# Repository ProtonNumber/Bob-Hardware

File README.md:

# Bob!

This is the Kicad Repo for Bob, an open-source flight computer and data logger
for model rocketry.

## Specification
- MCU: Raspberry Pi [RP2040](https://datasheets.raspberrypi.com/rp2040/rp2040-datasheet.pdf) Dual Core Cortex M0+.
- Flash: 2 x Wimbond [W25Q128](https://www.winbond.com/resource-files/W25Q128JV%20RevI%2008232021%20Plus.pdf) 16 MiB Flash chips.
- IMU: QST [QMI8658C](https://www.qstcorp.com/upload/pdf/202301/13-52-25%20QMI8658A%20Datasheet%20Rev%20A.pdf) 16 G / 2048 DPS IMU
- Compass: QST [QMC5883L](https://datasheet.lcsc.com/szlcsc/QST-QMC5883L-TR_C192585.pdf)
- Barometer: HopeRF [HP203B](https://hoperf.com/data/upload/portal/20190307/HP203B_DataSheet_EN_V2.0.pdf)
- GPIO: 16 GPIO pins broken out, plus access to internal I2C bus.
- Pyro: 2 x Pyro channels with continuity detection and separate arming switch.

## Pin Assignments
| GPIO Pin | Usage             | Broken Out? | Notes                                             |
|----------|-------------------|-------------|---------------------------------------------------|
| GPIO 00  | -                 | Y           |                                                   |
| GPIO 01  | -                 | Y           |                                                   |
| GPIO 02  | -                 | Y           |                                                   |
| GPIO 03  | -                 | Y           |                                                   |
| GPIO 04  | -                 | Y           |                                                   |
| GPIO 05  | -                 | Y           |                                                   |
| GPIO 06  | -                 | Y           |                                                   |
| GPIO 07  | Fire Main         | N           |                                                   |
| GPIO 08  | Fire Drogue       | N           |                                                   |
| GPIO 09  | Compass Interrupt | N           |                                                   |
| GPIO 10  | IMU Interrupt 1   | N           |                                                   |
| GPIO 11  | IMU Interrupt 2   | N           |                                                   |
| GPIO 12  | I2C SDA           | Y           |                                                   |
| GPIO 13  | I2C SCL           | Y           |                                                   |
| GPIO 14  | Drogue Continuity | N           |                                                   |
| GPIO 15  | Main Continuity   | N           |                                                   |
| GPIO 16  | Flash SPI RX      | N           |                                                   |
| GPIO 17  | Flash SPI CS      | N           |                                                   |
| GPIO 18  | Flash SPI SCLK    | N           |                                                   |
| GPIO 19  | Flash SPI TX      | N           |                                                   |
| GPIO 20  | Buzzer            | N           | Buzzer is only powered when battery is connected. |
| GPIO 21  | Arming Signal     | Y           | Reads status of the ARM switch                    |
| GPIO 22  | -                 | Y           |                                                   |
| GPIO 23  | -                 | Y           |                                                   |
| GPIO 24  | -                 | Y           |                                                   |
| GPIO 25  | Status LED        | N           |                                                   |
| GPIO 26  | -                 | Y           | May be used as analogue input                     |
| GPIO 27  | -                 | Y           | May be used as analogue input                     |
| GPIO 28  | -                 | Y           | May be used as analogue input                     |
| GPIO 29  | -                 | Y           | May be used as analogue input                     |

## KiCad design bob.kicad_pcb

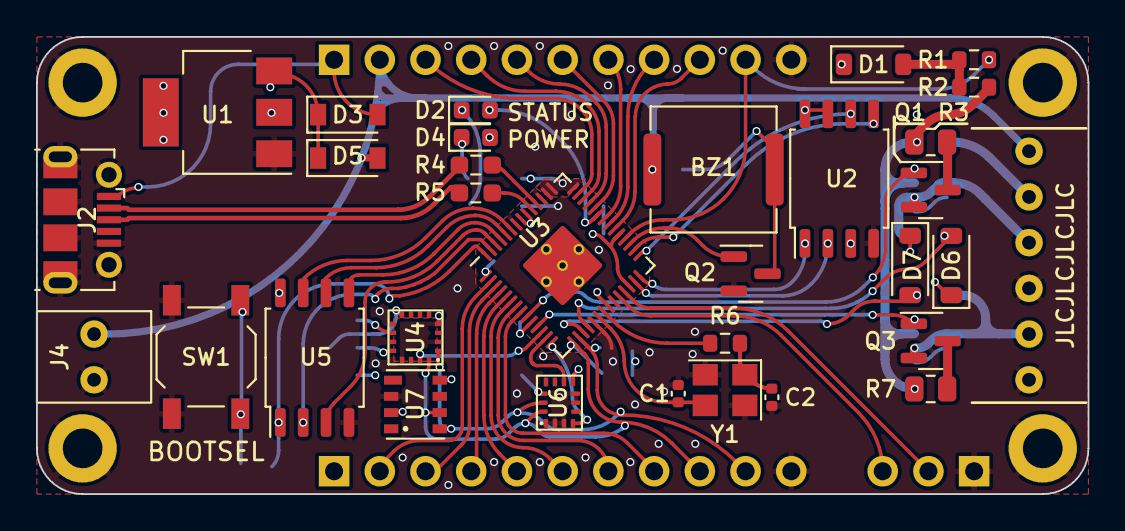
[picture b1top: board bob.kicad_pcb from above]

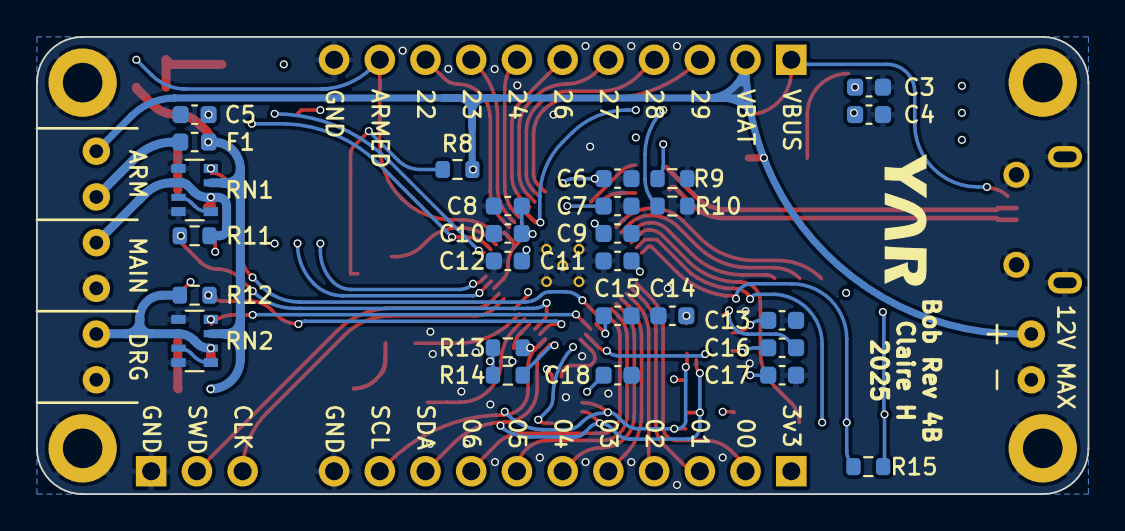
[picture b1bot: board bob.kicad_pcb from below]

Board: 4 copper layers, 58.4 x 25.4 mm, 67 parts (28 on the bottom side), 67 nets.

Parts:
BZ1: Buzzer; CPT-7502-65-SMT-TR
C1, C2: 7p; C_0402_1005Metric
C3, C4: 10u; C_0603_1608Metric
C5, C8, C9, C10, C11, C12, C14, C15, C17, C18: 100n; C_0603_1608Metric
C6, C7: 1u; C_0603_1608Metric
C13: 4.7u; C_0603_1608Metric
C16: 220n; C_0603_1608Metric
D1, D3, D5, D6, D7: B5819W SL; D_SOD-123
D2: GREEN; LED_0603_1608Metric
D4: RED; LED_0603_1608Metric
F1: Polyfuse; Fuse_0603_1608Metric
H1, H2, H3, H4: MountingHole_Pad; MountingHole_2.2mm_M2_DIN965_Pad
J1, J6: GPIO (Optional); PinHeader_1x11_P2.54mm_Vertical
J2: Micro USB Female; USB_Micro-B_Molex-105017-0001
J3: Conn_01x06_Pin; ScrewTerm_2.54x06
J4: Screw Terminal, 2.54mm; ScrewTerm_2.54x02
J5: Conn_01x03_Male; PinHeader_1x03_P2.54mm_Vertical
Q1, Q2, Q3: AO3400A; SOT-23
R1, R2, R13, R14: 3k6; R_0603_1608Metric
R3, R7: 5; R_0805_2012Metric
R4, R5: 27; R_0603_1608Metric_Pad0.98x0.95mm_HandSolder
R6, R8, R15: 1k; R_0603_1608Metric
R9: 470; R_0603_1608Metric
R10: 220; R_0603_1608Metric
R11, R12: 10k; R_0603_1608Metric
RN1, RN2: 10k; R_Array_Convex_4x0603
SW1: Bootsel; SW_SPST_TL3342
U1: AMS1117-3.3; SOT-223-3_TabPin2
U2, U5: W25Q128JVSS; SOIC-8_5.23x5.23mm_P1.27mm
U3: RP2040; RP2040-QFN-56
U4: QMC5883L; QMC5883L-LGA16
U6: QMI8658C; QMI8658C-LGA14
U7: HP203B; HP203B-LGA8
Y1: 12MHz; Crystal_SMD_3225-4Pin_3.2x2.5mm
YAR: LOGO; yar_new

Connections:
+1V1: C7.1, C12.1, U3.23 (DVDD), U3.45 (VREG_VOUT), U3.50 (DVDD)
+3V3: C4.1, C5.1, C6.1, C8.1, C9.1, C10.1, C11.1, C14.1, C15.1, C17.1, C18.1, D1.1 (K), D4.2 (A), D6.1 (K), D7.1 (K), J6.1, R13.2, R14.2, U1.2 (VO), U2.3 (IO2), U2.7 (IO3), U2.8 (VCC), U3.1 (IOVDD), U3.10 (IOVDD), U3.22 (IOVDD), U3.26 (RUN), U3.33 (IOVDD), U3.42 (IOVDD), U3.43 (ADC_AVDD), U3.44 (VREG_IN), U3.48 (USB_VDD), U3.49 (IOVDD), U4.2 (VDD), U4.4 (S1), U4.13 (VIO), U5.8 (VCC), U6.8 (VDD), U6.12 (CS), U7.3 (VDD), U7.8 (CSB)
+BATT: BZ1.1 (-), D5.2 (A), J1.2, J3.6, J4.2, R8.2
/Pyro 1/Fire +: J3.4, Q1.2 (S), R11.1, RN1.2 (R2.1), RN1.6 (R3.2)
/Pyro 2/Fire +: J3.2, Q3.2 (S), R12.1, RN2.2 (R2.1), RN2.6 (R3.2)
ARM: F1.2, R2.2, R3.1, R7.1, RN1.7 (R2.2), RN2.7 (R2.2)
ARMED: J1.10, R1.1, U3.32 (GPIO21)
BUZZER: Q2.1 (G), U3.31 (GPIO20)
Cont 1: D6.2 (A), R11.2, U3.18 (GPIO15)
Cont 2: D7.2 (A), R12.2, U3.17 (GPIO14)
GND: C1.1, C2.1, C3.2, C4.2, C5.2, C6.2, C7.2, C8.2, C9.2, C10.2, C11.2, C12.2, C13.1, C14.2, C15.2, C17.2, C18.2, H1.1, H2.1, H3.1, H4.1, J1.11, J2.5 (GND), J2.6 (Shield), J3.1, J3.3, J4.1, J5.1, J6.11, Q2.2 (S), R9.1, R10.2, RN1.1 (R1.1), RN1.4 (R4.1), RN2.1 (R1.1), RN2.4 (R4.1), SW1.1, U1.1 (GND), U2.4 (GND), U3.19 (TESTEN), U3.57 (GND), U4.9 (GND), U4.11 (GND), U5.4 (GND), U6.1 (SDO/SA0), U6.2 (SDX), U6.3 (SCX), U6.6 (GND), U6.7 (GND), U7.2 (GND), Y1.2, Y1.4
GPIO0: J6.2, U3.2 (GPIO0)
GPIO1: J6.3, U3.3 (GPIO1)
GPIO2: J6.4, U3.4 (GPIO2)
GPIO3: J6.5, U3.5 (GPIO3)
GPIO4: J6.6, U3.6 (GPIO4)
GPIO5: J6.7, U3.7 (GPIO5)
GPIO6: J6.8, U3.8 (GPIO6)
GPIO22: J1.9, U3.34 (GPIO22)
GPIO23: J1.8, U3.35 (GPIO23)
GPIO24: J1.7, U3.36 (GPIO24)
GPIO26: J1.6, U3.38 (GPIO26_ADC0)
GPIO27: J1.5, U3.39 (GPIO27_ADC1)
GPIO28: J1.4, U3.40 (GPIO28_ADC2)
GPIO29: J1.3, U3.41 (GPIO29_ADC3)
I2C_SCL: J6.10, R13.1, U3.16 (GPIO13), U4.1 (SCL), U6.13 (SCL), U7.5 (SCL)
I2C_SDA: J6.9, R14.1, U3.15 (GPIO12), U4.16 (SDA), U6.14 (SDA), U7.6 (SDA)
unnamed: BZ1.2 (+), Q2.3 (D), R8.1
unnamed: C2.2, R6.1, Y1.1
unnamed: C3.1, D3.1 (K), D5.1 (K), U1.3 (VI)
unnamed: D2.2 (A), U3.37 (GPIO25)
unnamed: D2.1 (K), R10.1
unnamed: D4.1 (K), R9.2
unnamed: D1.2 (A), R1.2, R2.1
unnamed: F1.1, J3.5
unnamed: Q1.3 (D), R3.2
unnamed: Q3.3 (D), R7.2
unnamed: R15.1, SW1.2
unnamed: RN1.3 (R3.1), RN1.5 (R4.2)
unnamed: RN2.3 (R3.1), RN2.5 (R4.2)
unnamed: C13.2, U4.10 (C1)
unnamed: C16.2, U4.12 (SETC)
unnamed: C16.1, U4.8 (SETP)
unnamed: R4.1, U3.46 (USB_DM)
unnamed: R5.1, U3.47 (USB_DP)
unnamed: C1.2, U3.20 (XIN), Y1.3
unnamed: R6.2, U3.21 (XOUT)
Pyro 1: Q1.1 (G), RN1.8 (R1.2), U3.9 (GPIO7)
Pyro 2: Q3.1 (G), RN2.8 (R1.2), U3.11 (GPIO8)
QMC_DRDY: U3.12 (GPIO9), U4.15 (DRDY)
QMI_INT1: U3.14 (GPIO11), U6.4 (INT1)
QMI_INT2: U3.13 (GPIO10), U6.9 (INT2)
QSPI_SCLK: U3.52 (QSPI_SCLK), U5.6 (CLK)
QSPI_SD0: U3.53 (QSPI_SD0), U5.5 (DI(IO0))
QSPI_SD1: U3.55 (QSPI_SD1), U5.2 (DO(IO1))
QSPI_SD2: U3.54 (QSPI_SD2), U5.3 (IO2)
QSPI_SD3: U3.51 (QSPI_SD3), U5.7 (IO3)
QSPI_SS: R15.2, U3.56 (QSPI_SS), U5.1 (~CS)
SPI_CS: U2.1 (~CS), U3.28 (GPIO17)
SPI_RX: U2.2 (DO(IO1)), U3.27 (GPIO16)
SPI_SCLK: U2.6 (CLK), U3.29 (GPIO18)
SPI_TX: U2.5 (DI(IO0)), U3.30 (GPIO19)
SWCLK: J5.3, U3.24 (SWCLK)
SWD: J5.2, U3.25 (SWD)
USB_D+: J2.3 (D+), R5.2
USB_D-: J2.2 (D-), R4.2
VBUS: D3.2 (A), J1.1, J2.1 (VBUS)

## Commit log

2022-07-04 Add kicad files
2022-07-04 Removed gbr files, fixed gitignore
2022-07-04 Rearranged directories
2022-07-04 Fixed issues with USB impedance
2022-07-24 Fixed MPU6050 charge pump cap
2022-07-24 Replaced BMP180 with HP203B
2022-07-24 Added piezo buzzer
2022-07-24 Moved I2C to bottom of RP2040
2022-07-24 Changed 0402s to 0603s
2022-07-24 Added SWD connector and test points
2022-07-24 Broke out VBAT
2022-07-25 Added a magnetometer
2022-07-28 Rev 3, issued for production
2022-07-28 Added addresses to I2C bus
2022-07-28 Fixed issues and reissued for production
2022-08-22 Added address for QMC5883L
2022-08-22 Added Kicad Libs. Added thermal relief.
2022-08-22 Added nice symbols to schematic
2022-08-22 Changed LED current limiter so it wont be so bright
2022-08-22 Changed SW1 to a button
2022-08-22 Nope, switch wont fit :(
2022-08-22 Updated footprints to be much saner
2022-08-22 Removed old libs
2022-08-22 Changed U3 to the new symbol libs
2022-08-23 Removed #auto_saved_files#
2022-08-23 Updated Libs
2022-09-06 Updated documentation
2022-09-07 Fixed very minor alignment issue that was annoying me.
2022-11-08 Added pyro channels Added bendy traces Added status LED Removed buzzer
2022-11-11 Started work on bob R4
2022-11-28 Corrected memory miscalculation and added the documentation
2023-07-08 Restructure repo
2023-07-08 Create LICENSE
2023-08-12 Fix submodules
2023-08-12 Swap out components to match LCSC stock
2023-08-12 Add dedicated flash for data
2023-08-12 Return of the buzzer
2023-08-23 Re-add gitignore
2023-08-23 Rev 4 issued for production
2023-08-23 Add readme
2023-08-24 Moved via from HP203 SCK pad
2025-02-28 Add current limit resistor between pyro channel and pin.
2025-02-28 Change to piezo buzzer in stock, add parallel resistor per manufacturer's guidance
2025-02-28 Reroute PCB to match changes in schematic
